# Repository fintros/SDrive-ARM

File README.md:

# SDrive-ARM
Atari800 disk drives emulator based on C.P.U. project SDrive

## Specs
- SDrive was developed originally by C.P.U. team in 2008 and use AT Mega 8 processor;
- It is extension of previous project with following features:
  - Works with Atari 8-bit systems like Atari 800, 800xl, XE/GS, etc.
  - 5V compatible 32bit Cypress CY8C4245AXI ARM processor with:
    - 48 MHz core
    - 32Kb Flash
    - 4Kb RAM
  - MicroSD card reader
  - Capacitive buttons (Next drive, Prev drive, Boot drive)
  - 6 LEDs (1 green, 1 red and 4 yellow)
  - Reset button
  - Each SIO pin connected to ARM I/O pin (Possibility for functionality extension)
  - One RW/RO switch for microSD card
  - original drive ID's switchng DIPs excluded
  
## Software needed to open and compile source code
- PCBs created in Eagle software (http://www.autodesk.com/products/eagle/overview)
- ARM firmware created in Cypress PSoC Creator 4.0 (http://www.cypress.com/products/psoc-creator-integrated-design-environment-ide)
- Box sketches created in Sketchup (http://www.sketchup.com/)

## Hardware needed to initial chip programming
- Cypress KitProg is needed to program ARM chip. Easiest way is to buy CY8CKIT-043 ($10) or similar kit  

## ToDo list
- [X] Fix an issue with daisy-chain connection (add switchng diode to SIO data in line)
- [X] Implements SDHC support
- [X] Implement FAT32 support
- [X] Add "Update from SD" feature
- [X] Apply Hias patches to firmware
- [X] Increase number of usable drives up to 8
- [ ] Implement cassete recorder functionality

## Contacts
- Please contact me in case of questions by E-Mail: extmail __at__ alsp.net
- Donations are welcomed to the same PayPal address ;)

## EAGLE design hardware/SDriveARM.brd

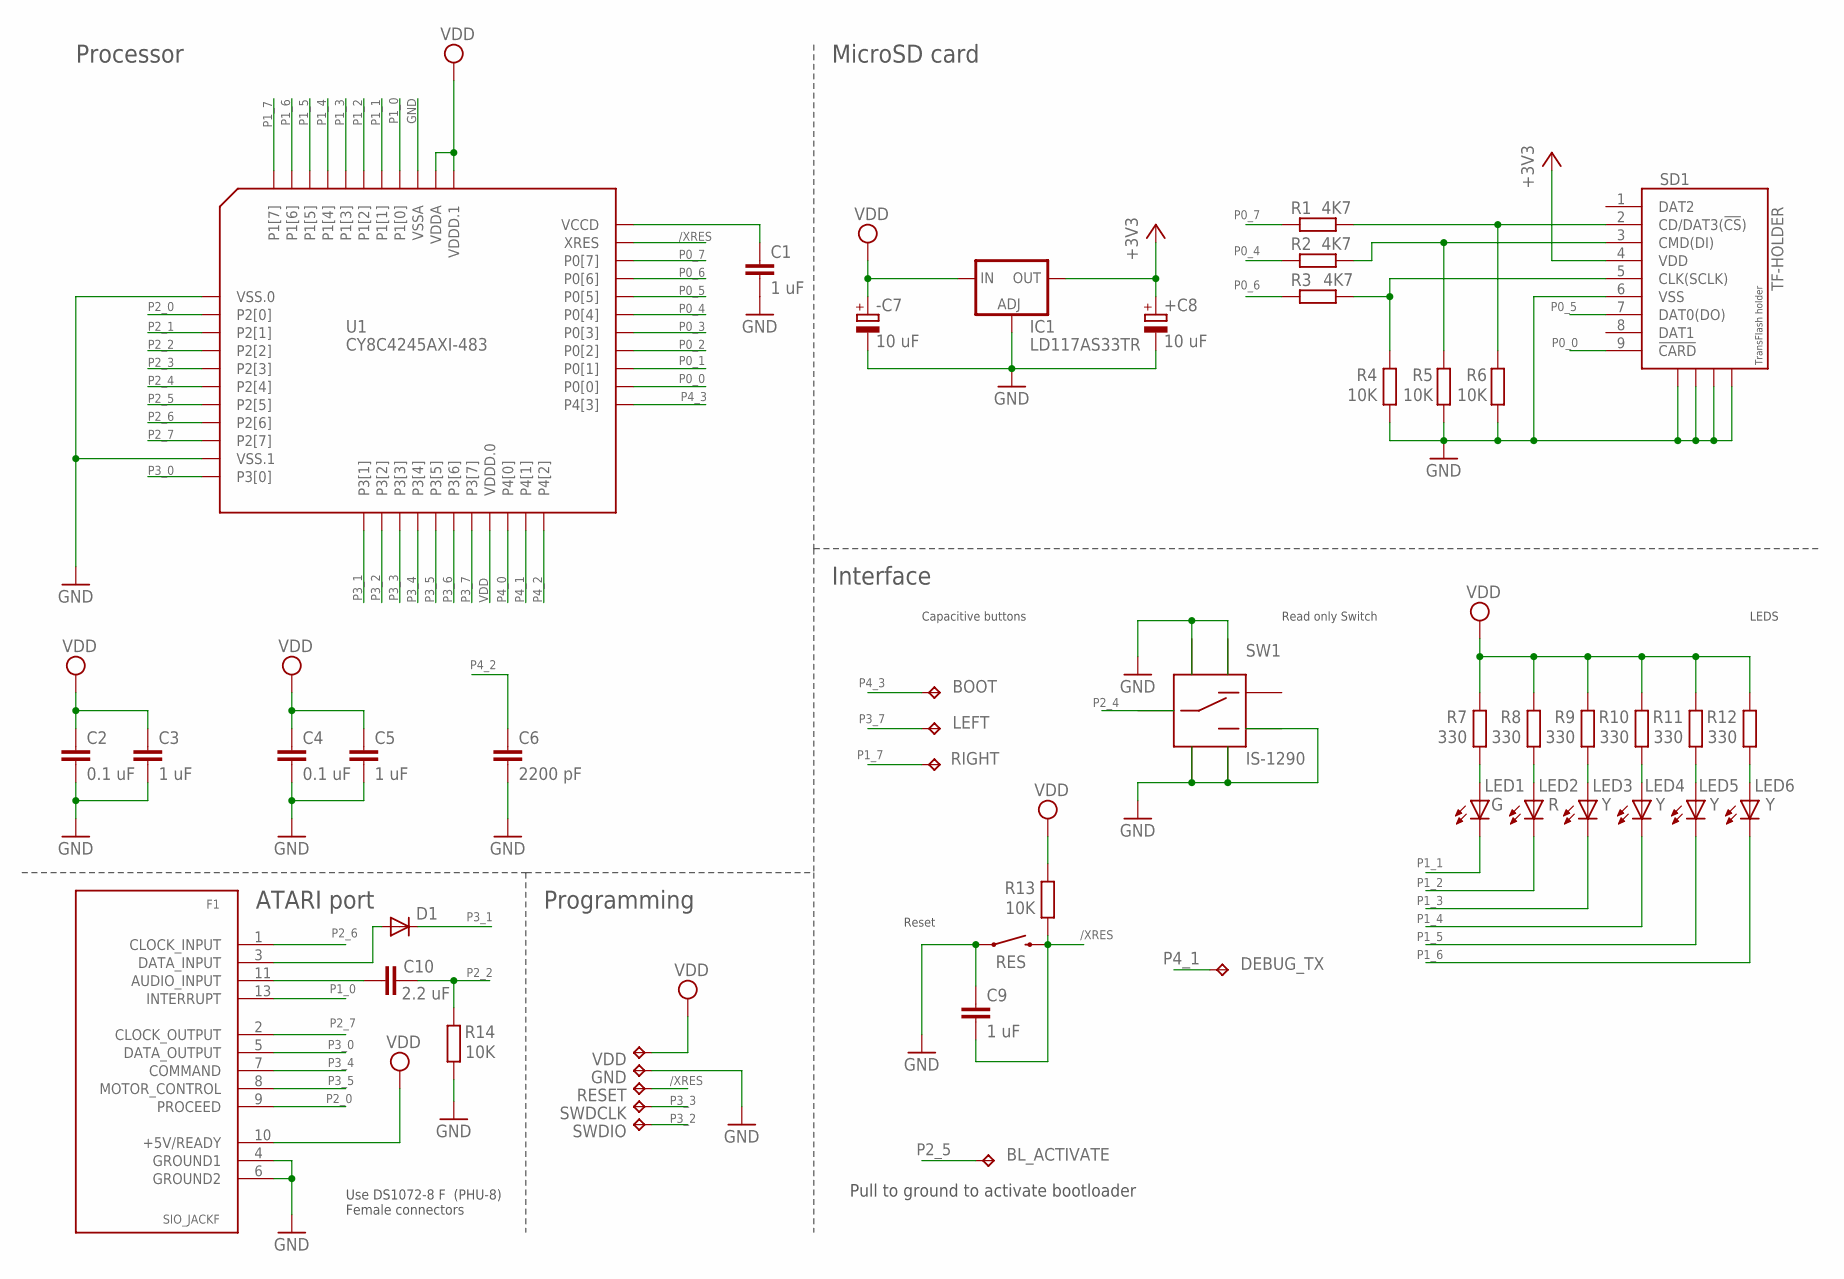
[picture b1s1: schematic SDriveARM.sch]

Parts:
+C8: 10 uF; A/3216-18W
-C7: 10 uF; A/3216-18W
BL_ACTIVATE: TPB1,27; B1,27
BOOT: TPTP20SQ; TP20SQ
C1, C3, C5, C9: 1 uF; C0603
C2, C4: 0.1 uF; C0603
C6: 2200 pF; C0603
C10: 2.2 uF; C0603
D1: MBR0520LT; SOD123
DEBUG_TX: TPB1,27; B1,27
F1: SIO_JACKF; SIO_JACK_F
GND: TPB1,27; B1,27
IC1: LD117AS33TR; SOT223
LED1: G; SML0805
LED2: R; SML0805
LED3, LED4, LED5, LED6: Y; SML0805
LEFT: TPTP20SQ; TP20SQ
R1, R2, R3: 4K7; R0603
R4, R5, R6, R13, R14: 10K; R0603
R7, R8, R9, R10, R11, R12: 330; R0603
RES: SWITCH-MOMENTARY-2; TACTILE_SWITCH_TALL
RESET: TPB1,27; B1,27
RIGHT: TPTP20SQ; TP20SQ
SD1: TF-HOLDER; TF-PULL
SW1: IS-1290
SWDCLK: TPB1,27; B1,27
SWDIO: TPB1,27; B1,27
U1: CY8C4245AXI-483; TQFP44
VDD: TPB1,27; B1,27

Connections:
+3V3: +C8.+, IC1.4 (OUT), SD1.4 (VDD)
/XRES: C9.2, R13.1, RES.B2 (2), RESET.TP, U1.32 (XRES)
GND: +C8.-, -C7.-, C1.2, C2.2, C3.2, C4.2, C5.2, C6.2, C9.1, F1.4 (GROUND1), F1.6 (GROUND2), GND.TP, IC1.1 (ADJ), R4.1, R5.1, R6.1, R14.1, RES.A2 (1), SD1.6 (VSS), SD1.S1, SD1.S2, SD1.S3, SD1.S4, SW1.POS2, SW1.SHIELD$1, SW1.SHIELD$2, SW1.SHIELD$3, SW1.SHIELD$4, U1.1 (VSS.0), U1.10 (VSS.1), U1.36 (VSSA)
unnamed: C1.1, U1.33 (VCCD)
unnamed: C10.2, F1.11 (AUDIO_INPUT)
unnamed: D1.A, F1.3 (DATA_INPUT)
unnamed: R1.2, R6.2, SD1.2 (CD/DAT3(!CS!))
unnamed: R2.2, R5.2, SD1.3 (CMD(DI))
unnamed: R3.2, R4.2, SD1.5 (CLK(SCLK))
unnamed: LED1.A, R7.1
unnamed: LED2.A, R8.1
unnamed: LED3.A, R9.1
unnamed: LED4.A, R10.1
unnamed: LED5.A, R11.1
unnamed: LED6.A, R12.1
P0_0: SD1.9 (!CARD), U1.24 (P0[0])
P0_1: U1.25 (P0[1])
P0_2: U1.26 (P0[2])
P0_3: U1.27 (P0[3])
P0_4: R2.1, U1.28 (P0[4])
P0_5: SD1.7 (DAT0(DO)), U1.29 (P0[5])
P0_6: R3.1, U1.30 (P0[6])
P0_7: R1.1, U1.31 (P0[7])
P1_0: F1.13 (INTERRUPT), U1.37 (P1[0])
P1_1: LED1.C, U1.38 (P1[1])
P1_2: LED2.C, U1.39 (P1[2])
P1_3: LED3.C, U1.40 (P1[3])
P1_4: LED4.C, U1.41 (P1[4])
P1_5: LED5.C, U1.42 (P1[5])
P1_6: LED6.C, U1.43 (P1[6])
P1_7: RIGHT.TP, U1.44 (P1[7])
P2_0: F1.9 (PROCEED), U1.2 (P2[0])
P2_1: U1.3 (P2[1])
P2_2: C10.1, R14.2, U1.4 (P2[2])
P2_3: U1.5 (P2[3])
P2_4: SW1.COMMON, U1.6 (P2[4])
P2_5: BL_ACTIVATE.TP, U1.7 (P2[5])
P2_6: F1.1 (CLOCK_INPUT), U1.8 (P2[6])
P2_7: F1.2 (CLOCK_OUTPUT), U1.9 (P2[7])
P3_0: F1.5 (DATA_OUTPUT), U1.11 (P3[0])
P3_1: D1.C, U1.12 (P3[1])
P3_2: SWDIO.TP, U1.13 (P3[2])
P3_3: SWDCLK.TP, U1.14 (P3[3])
P3_4: F1.7 (COMMAND), U1.15 (P3[4])
P3_5: F1.8 (MOTOR_CONTROL), U1.16 (P3[5])
P3_6: U1.17 (P3[6])
P3_7: LEFT.TP, U1.18 (P3[7])
P4_0: U1.20 (P4[0])
P4_1: DEBUG_TX.TP, U1.21 (P4[1])
P4_2: C6.1, U1.22 (P4[2])
P4_3: BOOT.TP, U1.23 (P4[3])
VDD: -C7.+, C2.1, C3.1, C4.1, C5.1, F1.10 (+5V/READY), IC1.3 (IN), R7.2, R8.2, R9.2, R10.2, R11.2, R12.2, R13.2, U1.19 (VDDD.0), U1.34 (VDDD.1), U1.35 (VDDA), VDD.TP

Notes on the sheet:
Read only Switch
Capacitive buttons
Programming
MicroSD card
Interface
Processor
ATARI port
Reset
LEDS
Pull to ground to activate bootloader
Use DS1072-8 F (PHU-8) Female connectors

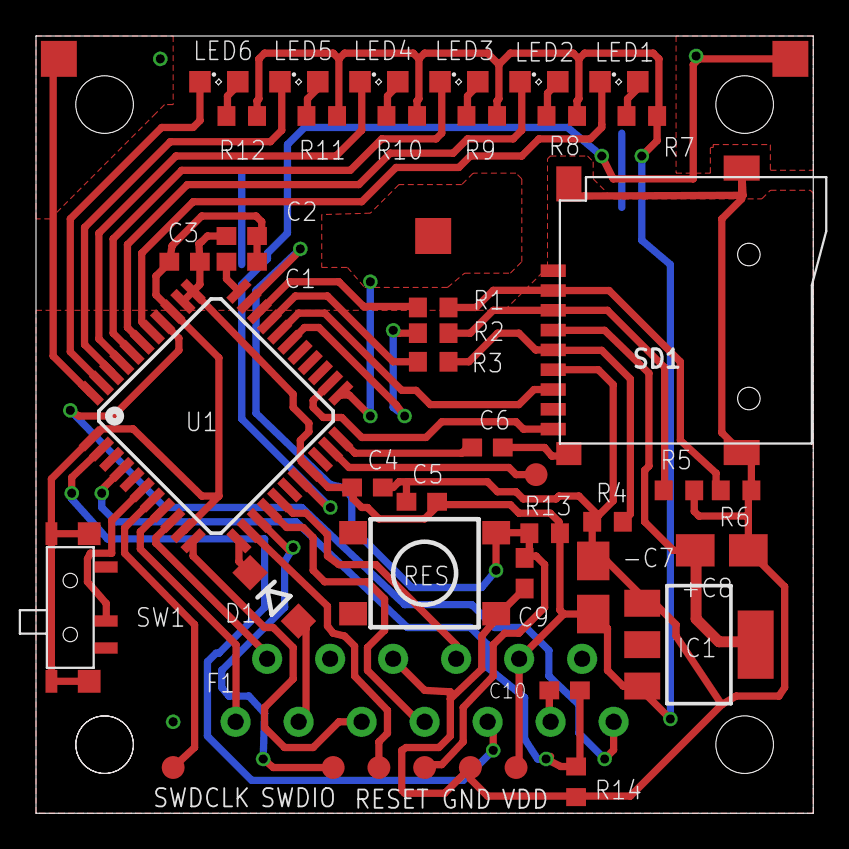
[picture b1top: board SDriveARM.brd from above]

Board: 2 copper layers, 43.2 x 43.2 mm, 47 parts (0 on the bottom side), 45 nets.

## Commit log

2016-12-02 :space_invader: Added .gitattributes & .gitignore files
2016-12-02 Initial version
    based on Bob!k & Raster, C.P.U., 2008 works
2016-12-02 Port To Cypress PSoC4 platform
    Adapted to CY8CKIT-049-42XX module
2016-12-02 Add binary ignore
2016-12-02 Cleanup scheme
2016-12-02 Add LEDS and buttons
2016-12-06 Switch to CapSense buttons
2017-02-14 Reorganize, add Box for 3D printing and PCB source and gerber files
2017-02-14 Add's documents and photos
2017-02-14 Add SD files and native source code
2017-02-17 Add small picture
2017-02-23 SDHC support, FAT32 support
2017-02-26 Add 8 drives support
    8 drives working, but configurations for 8 drives not saved yet - ToDo
2017-02-26 Remove unused CFG
2017-03-04 Update HW design to v1.1
    Add diode to "SIO data in" to allow work in chain
2017-03-05 Fix config load/save behavior for 8 drives
2017-03-05 Fix bug with FAT32 directory listing
2017-03-07 Update README.md
    Add "done" features
2017-04-01 Bootloader temp
    Temporary version of bootloader
2017-04-02 Fix bootloader adresses and slow down bug
2017-04-02 Working Update from SD
    Need to be cleaned yet , but it works!
2017-04-05 First stable version of bootloader
    Version stabilized, prebuilt bootloader binaries prepared to use
2017-07-10 Fix issue with misalligned access with FAT16
    There was bug detected with FAT16 operations on ARM.
    To fix it in bootloader, bootloader updater is needed
2017-07-29 Apply HiaS patches to firmware
2017-10-04 Fix bootloader to support Kingston 2Mb cards
    Some card would not to initialize with current sequence, but after reset
    works fine. Simulate reset in error cases
2017-10-04 Update version of FW + bootloader version detection
    Adds functionality to skip update with different bootloader version and
    update current version
2017-11-26 Start of whole code refactoring
2018-10-30 Intermediate changes
    Continue to rework
2018-11-08 Fix issue with 256-byte sectors
2018-11-09 Update to 3rd version of FW
2018-11-09 Fix FAT16 issue with bootloader version 1
2018-11-09 Adds update binaries and update manual
2020-09-06 ATX support beta
2020-09-14 Initial refactor
2020-09-28 Second try of refactoring
    Still lot of bugs exist
2020-09-29 Working refactored code
    Main functionalities are working now. Some checks still needed
2020-09-30 Fix LED bugs
2020-10-08 Second UART added - non stable
2020-10-10 Complete secondary UART
2020-10-10 SlowUART addon
2020-10-10 SlowUART comments are added
2020-10-11 ATX works start
    Not fully workable
2020-10-14 ATX works
    Half 60% images works
2020-10-25 Additiona ATX fixes
    Still some ATX not works -postponed for future time
    Dropzone, World Karate Championship and Ghost busters
2020-10-25 Tape support base
    Tape support added - to be fully functional configuration mechanizsms should be implemented on Atari side and on FW side
2020-11-08 Setting read initial version
    NB! not fully works.
2020-11-13 Config file works prerelease
    Config read is done - need to be tested
2020-11-14 Config write + code formating
2020-11-15 Fix config write issues
2020-11-18 Optimize size
2020-11-18 Fix settings propagation
2020-11-18 Add commands for config and tape
2022-09-16 Fix 3d models for printing

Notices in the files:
parts and their libraries:
atari: Copyright (c) 2010
Copyright (c) 2009
This library is licensed under the
Creative Commons Attribution 3.0 United States License.
SparkFun-Electromechanical: Licensing: CC v3.0 Share-Alike You are welcome to use this library for commercial purposes.
